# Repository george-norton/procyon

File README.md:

# Procyon

Procyon is an experimental trackpad similar to, but different from [Peacock](https://github.com/george-norton/peacock).
The PCBs themselves are small and I intend to add more sizes over time. Unlike Peacock, these are not standalone devices, they are intended to be
built into QMK/ZMK keyboards.

## Differences from Peacock

- Removed the separate LDO for AVCC - it all runs of the VIK 3.3v line which is preferable for wireless builds.
- Added a MOSFET to allow cutting power to the module, again this is a power saving feature for ZMK.
- The PCB is 4-layers with all the components mounted on the reverse of the sensor.
- Far smaller sensor areas.
- No integrated controller - these are meant for integrating into your own builds.

## Sensor capabilities

The mXT336UD-MAU002 sensor IC used in this design is in fact a touchscreen controller rather than a trackpad controller. I have chose this controller for Peacock as I wanted something that could support a large trackpad, and I have reused it here so I can reuse the code I wrote for Peacock.
- Detect 10 concurrent touch events.
- Can support both mutual capacitance and self capacitance measurements.
- Has integrated signal processing capabilities to reduce noise, reject large touches (grip or palms) etc..
- Can be configured as a digitizer, or an array of up to 16 buttons.
- The sensor also supports a passive stylus, the trackpads themselves are a litle small - but it works.

## Naming

Like Peacock, Procyon is named after a navigational star.

## Assembly

Procyon can be assembled by JLCPCB, or your favorite factory. Alternatively, if you feel brave, the components are not too tiny (0603) so it can be assembled on a small hotplate (such as the MHP50), you will probably need a stencil, and paste suitable for narrow apertures. The component placement (other than the optional button) is common between boards, so the same stencil can be reused.

The 57x80 variant has an optional footprint for a button. This button is wired to a GPIO on the MaxTouch IC and is accessable through the MaxTouch GPIO interface.

## Surfaces

A surface is required for the sensor to function. This should be an insulator, it should also feel nice since you will be touching it a lot. It is a good idea to fix the sensor to the board with glue or double sided tape. Good surface materials include:
- Vinyl
- PLA (printed at 0.5-1.6mm thickness - 100% infil)
- Acrylic (will need tuning tweaks if its thick)

## Wiring it up

- The easiest way to wire up a Procyon is via the [VIK](https://github.com/sadekbaroudi/vik) interface. Usually this requires a 12P 0.5mm pitch type A FFC cable. But For the Dilemma and SplitKB Halycon boards, you will need a type B cable instead.
- Alternatively you can solder wires to the pads on the board. You will need a minimum of VCC (3.3v), GND, SDA, SCL and CHG (connect to any GPIO pin).

## Software support

Currently there are experimental QMK and ZMK branches with Procyon support.

The [QMK multitouch_experiment branch](https://github.com/george-norton/qmk_firmware/tree/multitouch_experiment) exteneds the QMK digitizer feature to implement real trackpad support. On this branch, the MaxTouch driver reports 5 separate finger positions to the host and it detects gestures. You should get all the same gesture support you would expect from a modern trackpad. This branch is a large changeset which will likely take some time to get merged into QMK. There are some [pre-built QMK firmware images in my userspace](https://github.com/george-norton/qmk_userspace/releases/tag/latest).

The [ZMK Maxtouch module](https://github.com/george-norton/maxtouch-zephyr-module) builds against Petes [feat/pointers-move-scroll-ptp](https://github.com/petejohanson/zmk/tree/feat/pointers-move-scroll-ptp) ZMK branch. It is currently missing the ability to fallback to mouse emulation (so no MacOS support).

## Sensor tuning

The sensor sensitivity may require tuning depending on the type of surface you use on your build. This can be done by adjusting the touch threshold, and
if required the transmit gain. If your sensor is not detecting touches well, reduce the touch threshold. If your sensor is jittery, or is detecting spurious touches increase the touch threshold, or if there is any ungrounded metal by the sensor, move it. Increasing the transmit gain will require a larger touch threshold, but it should enable you to use thicker overlays and it will give you more room to adjust the touch threshold.

The mouse emulation gestures are implemented in software, they rely on various parameters that can be tuned by defining macros.

If you flash the QMK debug firmware, you can use the [Maxtouch debug](https://github.com/george-norton/maxtouch-debug) tool to adjust the sensor tuning in real time and see how it works.

## VIK certification

| Category                | Classification          | Response           |
| ----------------------- | ----------------------- | ------------------ |
| FPC connector           | Required                | :heavy_check_mark: |
| Breakout pins           | Recommended             | :x:                |
| Uses: SPI               | Optional                | :heavy_check_mark: |
| SPI used for SPI only   | Strongly recommended    | :heavy_check_mark: |
| Uses: I2C               | Optional                | :heavy_check_mark: |
| I2C used for I2C only   | Strongly Recommended    | :heavy_check_mark: |
| I2C pull ups            | Required                | 3.3k               |
| Uses: RGB               | Optional                | :x:                |
| Uses: Extra GPIO 1      | Optional                | :heavy_check_mark: |
| Uses: Extra GPIO 2      | Optional                | :heavy_check_mark: |
| Standard PCB Size/Mount | Strongly recommended    | :x:                |

## Schematic

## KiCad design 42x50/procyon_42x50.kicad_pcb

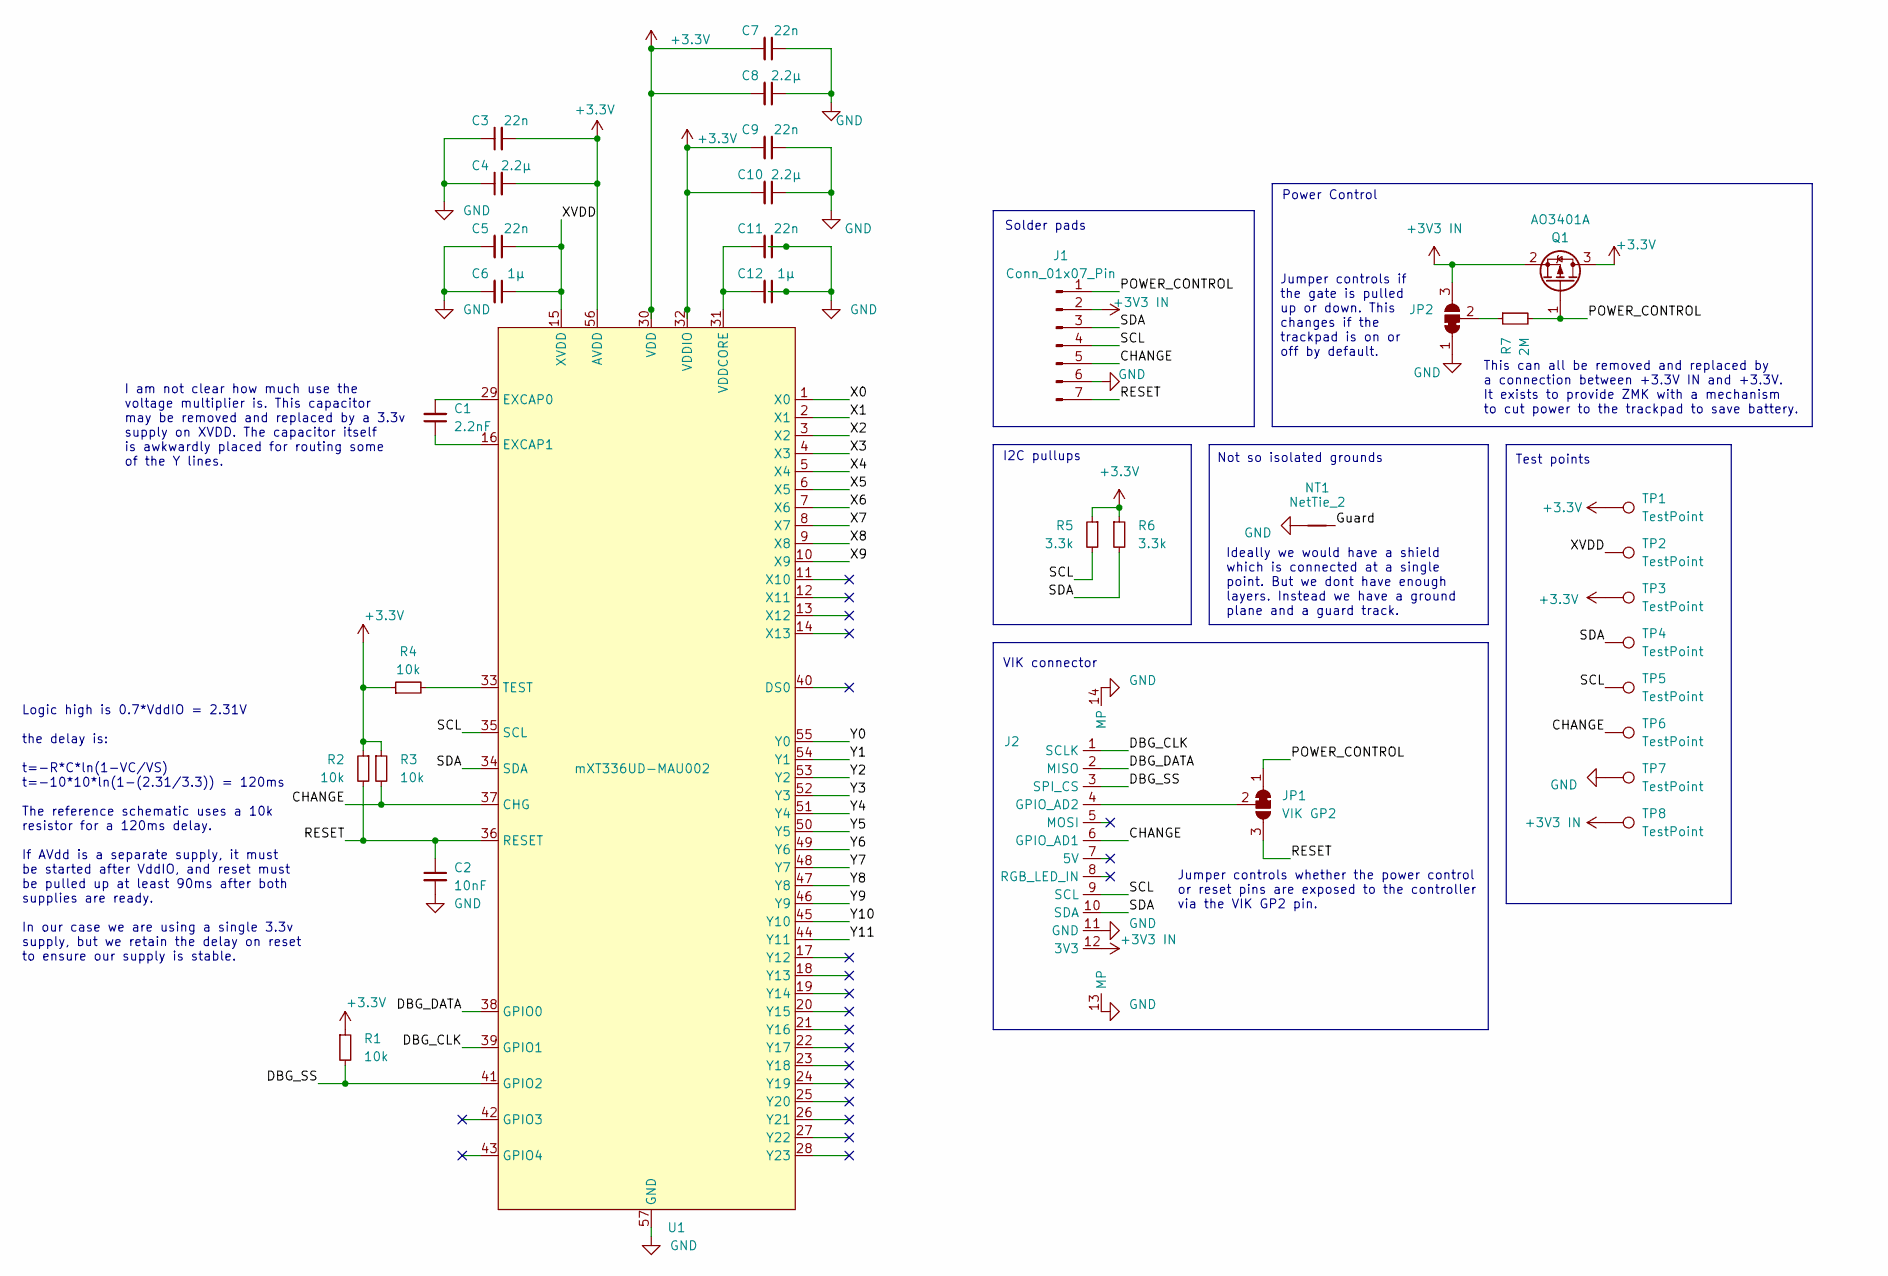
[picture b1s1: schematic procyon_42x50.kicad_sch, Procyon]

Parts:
C1: 2.2nF; C_0603_1608Metric; LCSC C1604
C2: 10nF; C_0603_1608Metric; LCSC C57112
C3, C5, C7, C9, C11: 22n; C_0603_1608Metric; LCSC C21122
C4, C8, C10: 2.2µ; C_0603_1608Metric; LCSC C23630
C6, C12: 1µ; C_0603_1608Metric; LCSC C15849
J1: Conn_01x07_Pin; Test Pads
J2: vik-module-connector-horizontal; LCSC C479750
JP1: VIK GP2; SolderJumper-3_P1.3mm_Bridged12_RoundedPad1.0x1.5mm_NumberL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
JP2: PWR; SolderJumper-3_P1.3mm_Bridged12_RoundedPad1.0x1.5mm_NumberL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
NT1: NetTie_2; NetTie-2_SMD_Pad0.5mm
Q1: AO3401A; SOT-23; LCSC C15127
R1, R2, R3, R4: 10k; R_0603_1608Metric; LCSC C25804
R5, R6: 3.3k; R_0603_1608Metric; LCSC C22978
R7: 2M; R_0603_1608Metric; LCSC C22976
TP1, TP2, TP3, TP4, TP5, TP6, TP7, TP8: TestPoint; TestPoint_Pad_D1.0mm
U1: mXT336UD-MAU002; QFN-56_EP_6x6_Pitch0.35mm; LCSC C5555867

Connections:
+3.3V: C3.2, C4.2, C7.2, C8.2, C9.2, C10.2, Q1.3 (D), R1.1, R2.1, R3.1, R4.1, R5.1, R6.1, TP1.1, TP3.1, U1.30 (VDD), U1.32 (VDDIO), U1.56 (AVDD)
+3V3 IN: J1.2, J2.12 (3V3), JP2.3 (B), Q1.2 (S), TP8.1
/CHANGE: J1.5, J2.6 (GPIO_AD1), R3.2, TP6.1, U1.37 (CHG)
/DBG_CLK: J2.1 (SCLK), U1.39 (GPIO1)
/DBG_DATA: J2.2 (MISO), U1.38 (GPIO0)
/DBG_SS: J2.3 (SPI_CS), R1.2, U1.41 (GPIO2)
/Guard: NT1.2
/POWER_CONTROL: J1.1, JP1.1 (A), Q1.1 (G), R7.2
/RESET: C2.1, J1.7, JP1.3 (B), R2.2, U1.36 (RESET)
/SCL: J1.4, J2.9 (SCL), R5.2, TP5.1, U1.35 (SCL)
/SDA: J1.3, J2.10 (SDA), R6.2, TP4.1, U1.34 (SDA)
/X0: U1.1 (X0)
/X1: U1.2 (X1)
/X2: U1.3 (X2)
/X3: U1.4 (X3)
/X4: U1.5 (X4)
/X5: U1.6 (X5)
/X6: U1.7 (X6)
/X7: U1.8 (X7)
/X8: U1.9 (X8)
/X9: U1.10 (X9)
/XVDD: C5.1, C6.1, TP2.1, U1.15 (XVDD)
/Y0: U1.55 (Y0)
/Y1: U1.54 (Y1)
/Y2: U1.53 (Y2)
/Y3: U1.52 (Y3)
/Y4: U1.51 (Y4)
/Y5: U1.50 (Y5)
/Y6: U1.49 (Y6)
/Y7: U1.48 (Y7)
/Y8: U1.47 (Y8)
/Y9: U1.46 (Y9)
/Y10: U1.45 (Y10)
/Y11: U1.44 (Y11)
GND: C2.2, C3.1, C4.1, C5.2, C6.2, C7.1, C8.1, C9.1, C10.1, C11.1, C12.1, J1.6, J2.11 (GND), J2.13 (MP), J2.14 (MP), JP2.1 (A), NT1.1, TP7.1, U1.57 (GND)
unnamed: J2.4 (GPIO_AD2), JP1.2 (C)
unnamed: JP2.2 (C), R7.1
unnamed: C1.2, U1.29 (EXCAP0)
unnamed: C1.1, U1.16 (EXCAP1)
unnamed: R4.2, U1.33 (TEST)
unnamed: C11.2, C12.2, U1.31 (VDDCORE)

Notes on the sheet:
I am not clear how much use the voltage multiplier is. This capacitor may be removed and replaced by a 3.3v supply on XVDD. The capacitor itself is awkwardly placed for routing some of the Y lines.
Logic high is 0.7*VddIO = 2.31V the delay is: t=-R*C*ln(1-VC/VS) t=-10*10*ln(1-(2.31/3.3)) = 120ms The reference schematic uses a 10k resistor for a 120ms delay. If AVdd is a separate supply, it must be started after VddIO, and reset must be pulled up at least 90ms after both supplies are ready. In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
Jumper controls if the gate is pulled up or down. This changes if the trackpad is on or off by default.
Solder pads
This can all be removed and replaced by a connection between +3.3V IN and +3.3V. It exists to provide ZMK with a mechanism to cut power to the trackpad to save battery.
I2C pullups
Jumper controls whether the power control or reset pins are exposed to the controller via the VIK GP2 pin.
Not so isolated grounds
Power Control
VIK connector
Ideally we would have a shield which is connected at a single point. But we dont have enough layers. Instead we have a ground plane and a guard track.
Test points

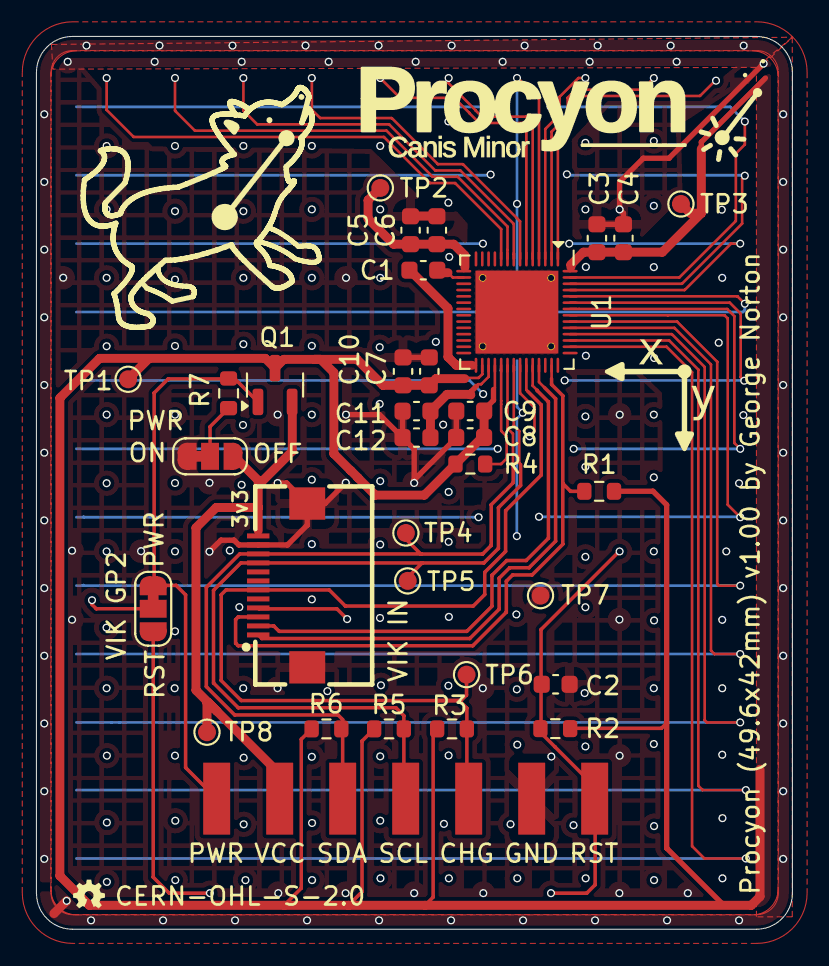
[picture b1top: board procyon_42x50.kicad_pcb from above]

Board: 4 copper layers, 42.0 x 49.6 mm, 34 parts (0 on the bottom side), 18 nets.

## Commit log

2024-10-14 Initial commit of the Procyon PCB.
2024-10-14 Reduce maxtouch IC paste coverage as we have reduced vias.
2024-10-16 Remove paste from the test pads.
2024-10-21 Swap from a 12x10 to a 10x12 matrix so we can use self capacitance measurements.
2024-10-21 Initial basic README.md.
2024-10-21 Add license.
2024-10-21 Add TP8.
2024-10-21 Mark the directions of the Axes on the silkscreen.
2024-10-27 Working changes
2024-10-28 Flip the power control jumper.
2024-10-28 Minor README update.
2024-10-30 Shuffle components to make space for more Y lines.
2024-11-07 Re-arrange into subfolders for different sized trackpads.
2024-11-08 Started work on 57x80.
2024-11-11 Completed routing for 57x80
2024-11-11 Fix inconsistent sense line width
2024-11-30 A bit more documentation.
2024-12-05 Add missing rule areas. Attempt to reduce paracitic capacitance.
2025-01-28 Extend the readme.
2025-02-19 Add VIK certification.

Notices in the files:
42x50/procyon_42x50.kicad_pcb:
CERN-OHL-S-2.0
